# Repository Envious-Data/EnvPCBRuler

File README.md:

# EnvPCBRuler
 
A ruler! rulers are very useful.

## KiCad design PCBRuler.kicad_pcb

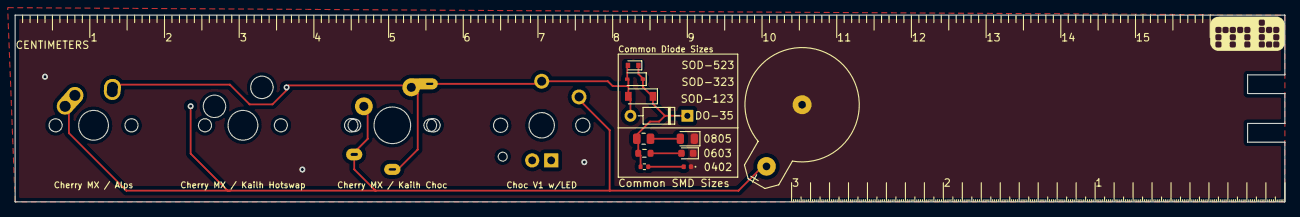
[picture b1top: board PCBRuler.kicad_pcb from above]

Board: 2 copper layers, 170.0 x 25.0 mm, 16 parts (0 on the bottom side), 7 nets.

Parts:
BT1: Battery_Cell; BatteryHolder_Keystone_500
D1: DIODE; D_SOD-123
D2: DIODE; D_SOD-323
D3: DIODE; D_DO-35_SOD27_P7.62mm_Horizontal
D4: LED; LED_0402_1005Metric
D5: LED; LED_0603_1608Metric
D6: LED; LED_0805_2012Metric
D9: DIODE; D_SOD-523
R1: R_Small; R_0402_1005Metric
R2: R_Small; R_0603_1608Metric
R3: R_Small; R_0805_2012Metric
Ref**: Val**; mechboardsLOGO_10mm
SW1: SW_PUSH; MX-1U-NoLED
SW2: SW_PUSH; MXOnly-1U-Hotswap
SW3: SW_PUSH; CherryMX_ChocV2_1u
SW4: SW_PUSH; KailhChoc-1U

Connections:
GND: BT1.2, D4.1, D5.1, D6.1
unnamed: BT1.1, SW1.1, SW2.1, SW3.1, SW4.1
unnamed: D1.1, D2.1, D3.1, D9.1, R1.2, R2.2, R3.2
unnamed: D1.2, D2.2, D3.2, D9.2, SW1.2, SW2.2, SW3.2, SW4.2
unnamed: D4.2, R1.1
unnamed: D5.2, R2.1
unnamed: D6.2, R3.1

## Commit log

2021-09-24 changed backside centimeters for inches with lines at 100mils, 50 and 10
2021-10-01 moved some parts about, changed battery holder, added markings to top and bottom on both sides (alternated)
